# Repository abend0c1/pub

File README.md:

PUB! Programmable USB Button
============================
Program a button to send keystrokes to your computer

PUB! is a Programmable USB Button on which you can program a sequence of keystrokes. When you press the button those keystrokes are "replayed" over a USB connection.

The button (really a rotary encoder with a built-in push button switch) is programmed using an innovative and slightly quirky interface that does not require any custom software to be installed on your computer. All you need is a text editor like Notepad or gedit.

Features
--------
- One-button design (a rotary encoder with a built in switch).
- Programmed by using an ordinary text editor as a display (for example, gedit on Linux, or Notepad on Windows).
- Up to 127 keystrokes can be recorded and played back.
- Support for conditional logic. For example, Compare to value, Jump on zero, etc.
- Support for 256 x 8-bit "registers" to record state.
- Support for basic arithmetic. Add, subtract, etc.
- Can send USB System Control codes (Power off, sleep, wake) to your PC
- Can send USB Consumer Device functions (e.g. Mute, Play, Pause, Stop, etc.)
- Requires NO drivers (or custom software) for Windows/Linux etc

Futures
-------
The possibilities are fairly broad including:
- Using a Bluetooth module to detect proximity of the button owner's mobile phone so that the USB button is only enabled when its owner is near.
- Addition of an external EEPROM for extra keystroke capacity.
- The one-button user interface could be improved to make it easier to use.

Construction
------------

See http://www.instructables.com/id/PUB-Programmable-USB-Button/

How To Use
----------
### You want to program your password onto the PUB! button
  - Open a text editing program (for example, gedit or Notepad) and make sure it has keyboard focus
  - Plug PUB! into a host USB port
  - By default it is in RUN mode, so press and hold the rotary encoder knob for more than 1 second to switch to PROGRAM mode. It will display in your text editor:

          PUB! Programmable USB Button v0.93
          Main:   Turn=Select, Press=OK, Press+Turn=Set At, Press+Hold=Exit
             0    Set Keystroke at 00
          At Code Action

  - Press the rotary knob to set a keystroke. It will display:

          PUB! Programmable USB Button v0.93
          Key:    Turn=Select, Press+Turn=Modify, Press=OK, Press+Hold=Return
          00 0004 a
          At Code Action

  - Turn the rotary knob to choose the first letter of your password (say c) and then press the knob to add it to the list of actions:

          PUB! Programmable USB Button v0.93
          Key:    Turn=Select, Press+Turn=Modify, Press=OK, Press+Hold=Return
          01 0006 c
          At Code Action
          00 0006 c

  - Continue choosing and adding the remaining letters (say, a and t):

          PUB! Programmable USB Button v0.93
          Key:    Turn=Select, Press+Turn=Modify, Press=OK, Press+Hold=Return
          03 0017 t
          At Code Action
          00 0006 c
          01 0004 a
          02 0017 t

  - Press and hold the rotary knob to Return to the main menu:

          PUB! Programmable USB Button v0.93
          Main:   Turn=Select, Press=OK, Press+Turn=Set At, Press+Hold=Exit
             0    Set Keystroke at 03
          At Code Action
          00 0006 c
          01 0004 a
          02 0017 t

  - Rotate the knob until "Do Local Function" is displayed:

          PUB! Programmable USB Button v0.93
          Main:   Turn=Select, Press=OK, Press+Turn=Set At, Press+Hold=Exit
             0    Do Local Function at 03
          At Code Action
          00 0006 c
          01 0004 a
          02 0017 t

  - Press the knob to enter the "Do" menu:

            PUB! Programmable USB Button v0.93
            Do:     Turn=Modify, Press=OK, Press+Turn=Set At, Press+Hold=Exit
               0    Delete action at 00
            At Code Action
            00 0006 c
            01 0004 a
            02 0017 t

  - Press-and-rotate the knob anticlockwise until "Save to EEPROM" is displayed:

          PUB! Programmable USB Button v0.93
          Do:     Turn=Modify, Press+Turn=Select, Press=OK, Press+Hold=Return
                  Save to EEPROM
          At Code Action
          00 0006 c
          01 0004 a
          02 0017 t

  - Press the knob to save "cat" to the EEPROM

          Saved in EEPROM

  - The device is now in RUN mode. Press the knob to "play" the recorded sequence:

          cat

### An example of some conditional logic

  - Enter the following program into the PUB! device:

          At Code Action
          00 E005 Let W = 05
          01 E200 Put W in R00
          02 0006 c
          03 0004 a
          04 0017 t
          05 002C Space
          06 E500 Say R00
          07 0028 Enter
          08 EF01 Wait 1 sec
          09 E801 Let W = W - 01
          0A F701 Jump if Not Zero to 01

  - Now when you press the knob in run mode you should see the following displayed (1 second wait between lines):

          cat 05
          cat 04
          cat 03
          cat 02
          cat 01

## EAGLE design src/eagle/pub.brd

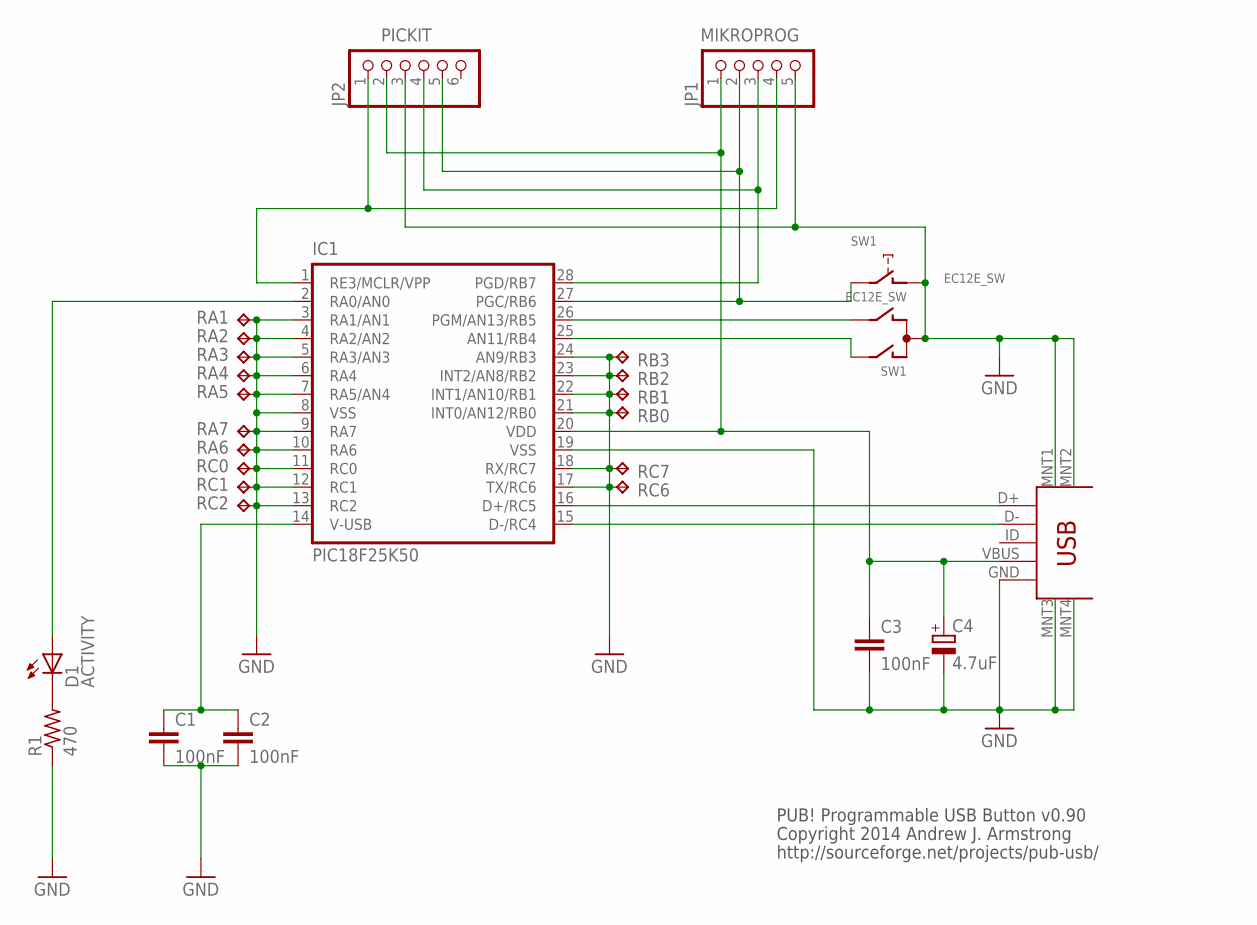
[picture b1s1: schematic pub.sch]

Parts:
C1, C2, C3: 100nF; C0805
C4: 4.7uF; SMC_A
D1: ACTIVITY; SML1206
IC1: PIC18F25K50; SO28W
JP1: MIKROPROG; 1X05/90
JP2: PICKIT; 1X06/90
JP3: USB-MINIB-5PIN; USB-MINIB
R1: 470; M1206
RA1, RA2, RA3, RA4, RA5, RA6, RA7: TPB1,27; B1,27
RB0, RB1, RB2, RB3: TPB1,27; B1,27
RC0, RC1, RC2, RC6, RC7: TPB1,27; B1,27
SW1: EC12E_SW; ALPS_EC12E_SW

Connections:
GND: C1.2, C2.2, C3.2, C4.-, IC1.3 (RA1/AN1), IC1.4 (RA2/AN2), IC1.5 (RA3/AN3), IC1.6 (RA4), IC1.7 (RA5/AN4), IC1.8 (VSS), IC1.9 (RA7), IC1.10 (RA6), IC1.11 (RC0), IC1.12 (RC1), IC1.13 (RC2), IC1.17 (TX/RC6), IC1.18 (RX/RC7), IC1.19 (VSS), IC1.21 (INT0/AN12/RB0), IC1.22 (INT1/AN10/RB1), IC1.23 (INT2/AN8/RB2), IC1.24 (AN9/RB3), JP1.5, JP2.3, JP3.GND, JP3.MNT1, JP3.MNT2, JP3.MNT3, JP3.MNT4, R1.1, RA1.TP, RA2.TP, RA3.TP, RA4.TP, RA5.TP, RA6.TP, RA7.TP, RB0.TP, RB1.TP, RB2.TP, RB3.TP, RC0.TP, RC1.TP, RC2.TP, RC6.TP, RC7.TP, SW1.C, SW1.D (1)
unnamed: IC1.26 (PGM/AN13/RB5), SW1.B
unnamed: IC1.25 (AN11/RB4), SW1.A
unnamed: C1.1, C2.1, IC1.14 (V-USB)
unnamed: D1.A, IC1.2 (RA0/AN0)
unnamed: IC1.16 (D+/RC5), JP3.D+
unnamed: IC1.15 (D-/RC4), JP3.D-
unnamed: C3.1, C4.+, IC1.20 (VDD), JP1.1, JP2.2, JP3.VBUS
unnamed: IC1.27 (PGC/RB6), JP1.2, JP2.5, SW1.E (2)
unnamed: IC1.28 (PGD/RB7), JP1.3, JP2.4
unnamed: IC1.1 (RE3/MCLR/VPP), JP1.4, JP2.1
unnamed: D1.C, R1.2

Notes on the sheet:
Copyright 2014 Andrew J. Armstrong
http://sourceforge.net/projects/pub-usb/
PUB! Programmable USB Button v0.90

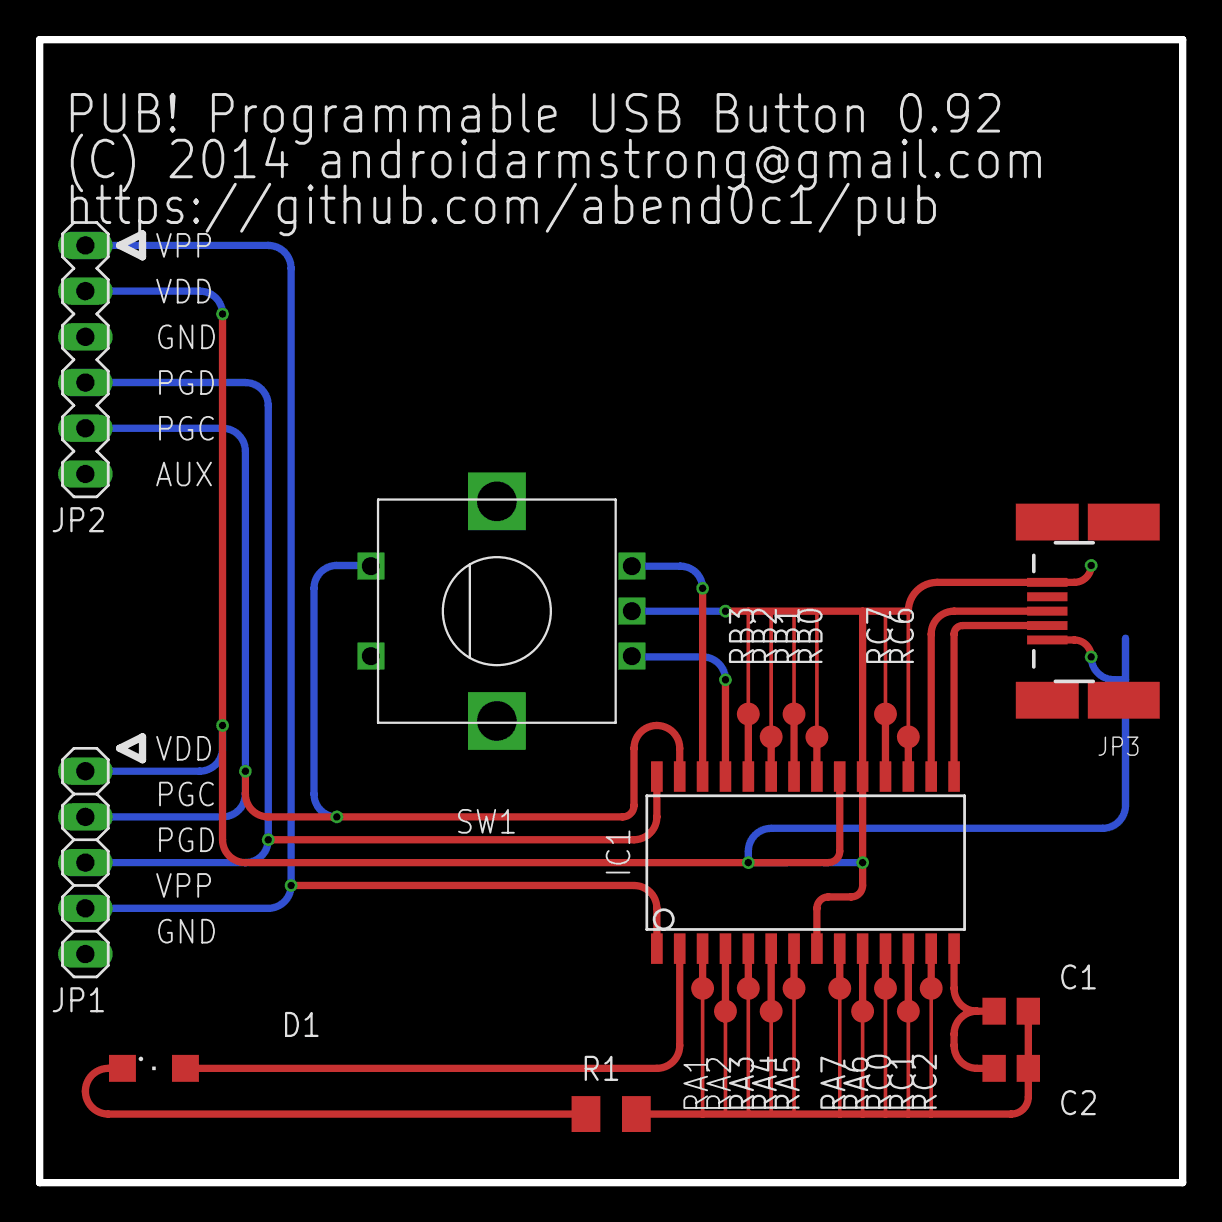
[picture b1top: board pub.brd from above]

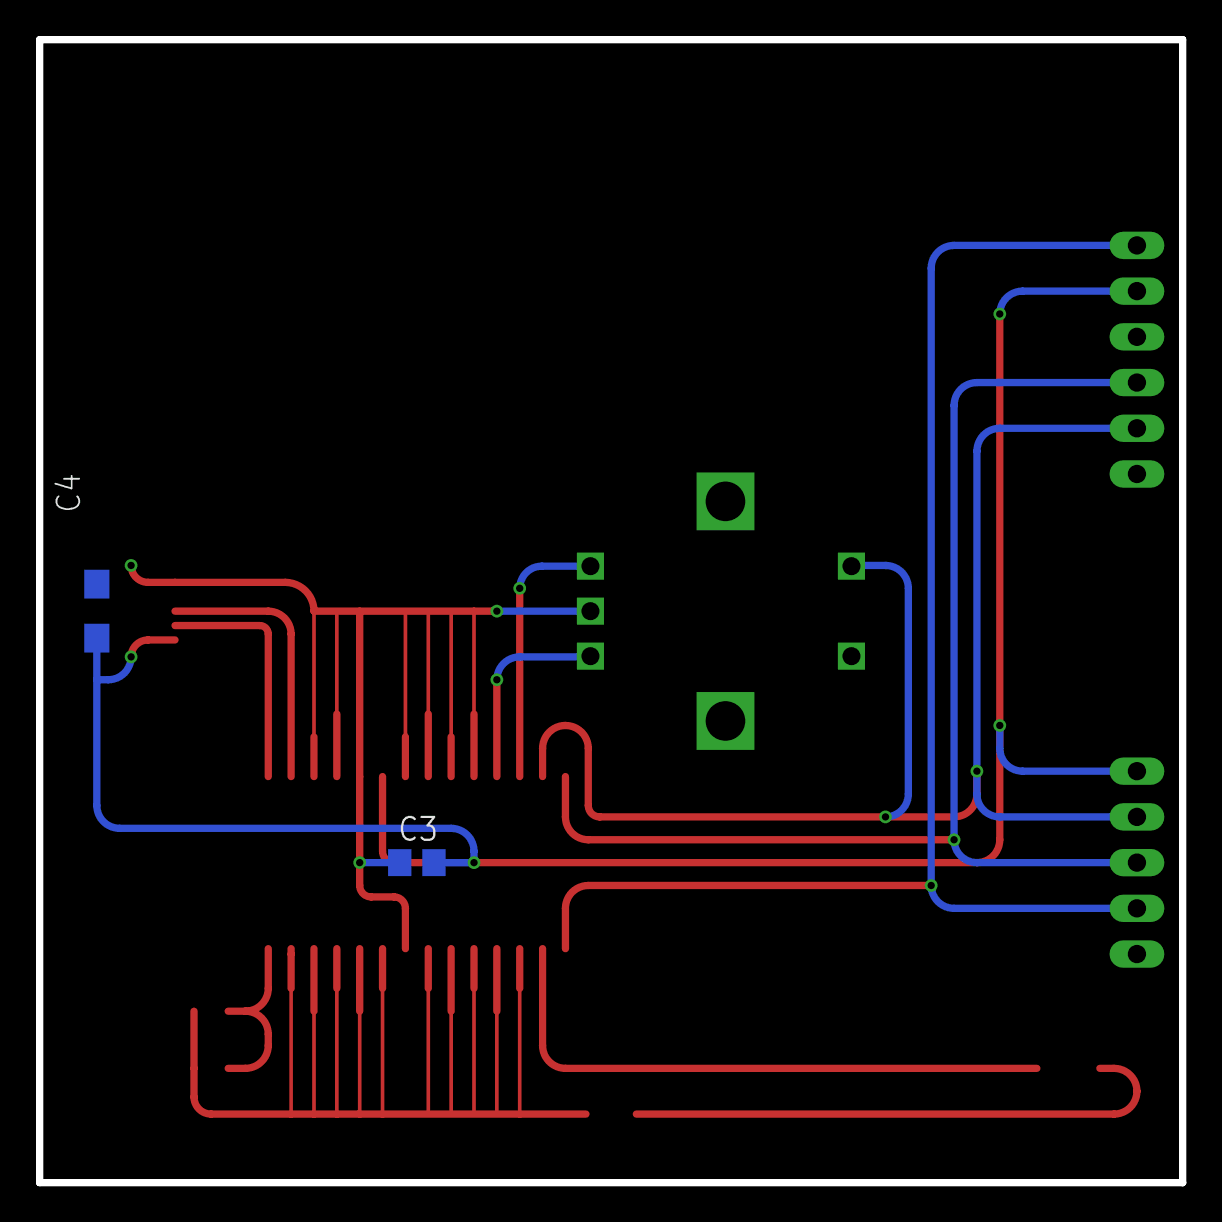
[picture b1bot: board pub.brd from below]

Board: 2 copper layers, 63.5 x 63.5 mm, 28 parts (2 on the bottom side), 12 nets.

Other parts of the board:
U$1: LIGHTGUIDE

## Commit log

2014-10-06 Initial version
2014-10-06 Removed inactivity timeout code. Refactored long press logic.
2014-10-06 Reworked delete action logic
2014-10-07 Renamed project to PUB! (Programmable USB Button) Added code to save to/load from EEPROM
2014-10-08 Updated load/save from EEPROM
2014-10-11 Fixed the 'Delete action' function
2014-10-11 Add debounce after button release
2014-10-11 Updated doco
2014-10-12 Correct display of Consumer Device actions
2014-10-12 Improved menu navigation
2014-10-12 Improved performance by not sending a "no key pressed" usage after every keystroke.
    The "no key pressed" is now only sent at the end
    of each string, and between sending the same keystroke (e.g. aaa),
    and when the "Wait n seconds" local function is used.
2014-10-23 Added Eagle CAD schematic and board
2014-10-25 Tweaked PCB slightly
2014-10-26 Created gerber files for the PCB
2014-10-26 Added product name to the PCB
2014-10-26 Adjust text on PCB
2014-10-26 Use ITEAD Studio's DRC and CAM job to create the gerber files
2014-10-26 Cleaned up pub.lbr
2014-10-27 Fixed unconnected trace on PCB. The ITEAD guys found it. I don't know how it missed that.
2014-11-03 Reworked PCB layout and changed to vector fonts
2014-11-09 Fixed PCB to match code. Rotary button on RB6
2014-11-10 Made superficial changes. TMR3IF_bit is used instead of explicit register and bit number. Updated ASCII art in the doco.
2014-11-12 Updated gerber files for v0.91 PCB layout
2014-11-13 Fix key playback to handle sending the same keystroke consecutively
2014-11-15 Used Timer0 for LED blinking instead of Timer3
2014-11-15 Removed obsolete project paths
2014-11-15 Passed parameters to playxxx functions
2014-11-15 Renamed LED to ACTIVITY_LED
2014-11-16 Update handling of playback interruption by user
2014-11-16 Fix the "user abort" button press logic.
    When the user requests to abort the playback by pressing the button
    the code now waits for any button press bouncing to subside, then
    it waits for the user to release the button, then waits for any
    button release bouncing to subside.
2014-11-17 Fixed typo in PICKIT header.
    How did I not see it spelled as PICKKIT? Sheesh!
2014-11-30 Added simple instructions like load/store, add/subtract, conditional jumps.
    This allows the user to create simple programs instead of
    just playing back keystrokes.
2014-11-30 Added CLEAR instruction
2014-12-01 Updated a few comments
2014-12-02 Added a PDF circuit diagram
2014-12-06 Added link to Instructables for construction steps
2014-12-06 Fixed grammar in README.md
2014-12-07 Decoded the FORMAT instruction into a human readable form
2014-12-07 Rename FORMAT instruction to 'SAY In'
2014-12-14 Updated PCB art
2015-02-15 Create gh-pages branch via GitHub
2015-02-16 Added image of prototype to README.md
2015-02-16 Added image of prototype
2015-02-16 Updated html to include image
2016-10-30 Detected the state of the Caps Lock LED indicator.
    Prior this update, if you coded SHIFT+A then the host interpreted
    that as either uppercase "A" or lowercase "a" depending on the
    current setting of the CAPS LOCK status. Now SHIFT+A will always
    be interpreted by the host as uppercase "A" because the device
    knows whether the CAPS LOCK LED is on or not. If CAPS LOCK is
    on, then the SHIFT modifier is reset so that the "a" is interpreted

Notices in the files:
src/eagle/pub.brd:
(C) 2014 androidarmstrong@gmail.com
